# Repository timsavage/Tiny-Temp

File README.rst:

########
TinyTemp
########

Had all the components laying about so this is a bit of a trial project for 
making my first PCB. 

Utilises a HP QDSP-6064 bubble display, a TMP34 temperature sensor, and an 
ATTiny85, will draw very little current for a longer life.

Hardware
========

The bubble displays can be hard to come by but they do pop up on Ebay from 
time to time.

Display is driven by a pair of 74HC595 IC's, one to control segments the other 
to switch transistors to pull Cathodes to ground. As the 74HC595 can be daisy
chained on 3 pins are required to drive the display. The TMP36 uses 1 ADC 
leaving one pin free.

Note that in the schematic the 3.3 Volt regulator used is the LD33V the pin
layout differs from the 78XX series in with:
 - Pin 1: GRN
 - Pin 2: OUT
 - Pin 3: IN

The schematic uses a 78XX series symbol.

The ICSP header is optional and only really in place for convenience.

BOM
---

 - 1x HP QDSP-6064 - 7 Segment "Bubble" display
 - 1x	ATTiny 85
 - 1x	TMP34 - Temperature sensor
 - 1x LD33V - 3.3V voltage regulator
 - 2x	74HC595 - Shift register
 - 4x	2N3904 - NPN transistor
 - 5x	10k ohm resistor
 - 4x	330 ohm resistor
 - 2x	0.1uF MLC cap

Software
========

Use the install target to build, upload, and set correct fuses for an ATTiny85
using a USBTiny programmer. These settings can be tweaked in the Makefile.

All pins, voltage levels (defaults to 3.3V) can be configured in *defines.h*.

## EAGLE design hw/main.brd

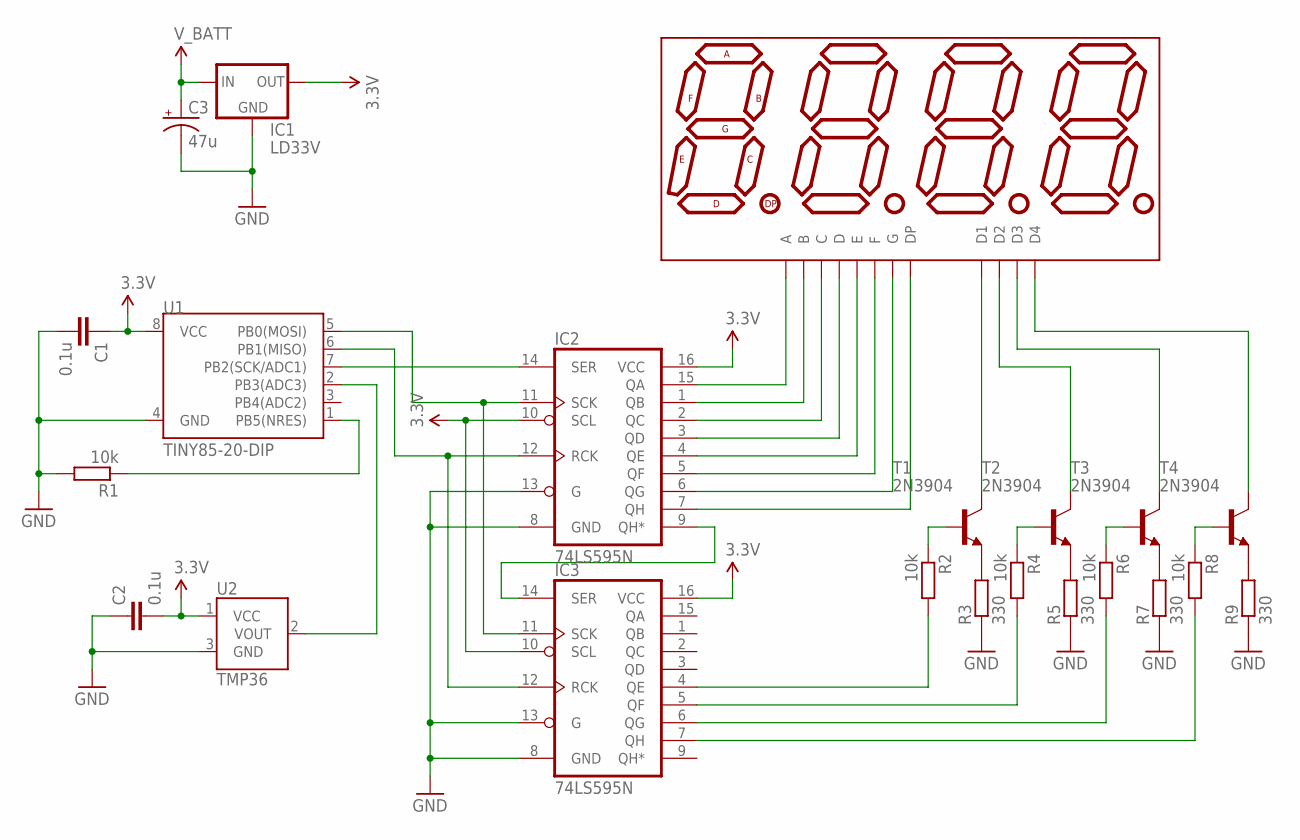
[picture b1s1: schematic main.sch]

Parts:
C1, C2: 0.1u; C025-025X050
C3: 47u; CPOL-RADIAL-10UF-25V
DISP1: 7-SEGMENT-4DIGIT-COUNTER-HP-BUBBLE; DIL12
IC1: LD33V; 78XXL
IC2, IC3: 74LS595N; DIL16
R1: 10k; 0204/7
R2, R4, R6, R8: 10k; 0204V
R3, R5, R7, R9: 330; 0204V
T1, T2, T3, T4: 2N3904; TO92
U1: TINY85-20-DIP; DIP08
U2: TMP36; TO-92

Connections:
GND: C1.2, C2.1, C3.2 (-), IC1.GND, IC2.8 (GND), IC2.13 (G), IC3.8 (GND), IC3.13 (G), R1.2, R3.1, R5.1, R7.1, R9.1, U1.4 (GND), U2.3 (GND); also elsewhere on the board
unnamed: DISP1.12 (A), IC2.15 (QA)
unnamed: DISP1.11 (B), IC2.1 (QB)
unnamed: DISP1.3 (C), IC2.2 (QC)
unnamed: DISP1.8 (D), IC2.3 (QD)
unnamed: DISP1.2 (E), IC2.4 (QE)
unnamed: DISP1.9 (F), IC2.5 (QF)
unnamed: DISP1.7 (G), IC2.6 (QG)
unnamed: DISP1.5 (DP), IC2.7 (QH)
unnamed: IC2.9 (QH*), IC3.14 (SER)
unnamed 10: IC2.11 (SCK), IC3.11 (SCK), U1.5 (PB0(MOSI)); also elsewhere on the board
unnamed 11: IC2.12 (RCK), IC3.12 (RCK), U1.6 (PB1(MISO)); also elsewhere on the board
unnamed: R3.2, T1.3 (E)
unnamed: R5.2, T2.3 (E)
unnamed: R9.2, T4.3 (E)
unnamed: R7.2, T3.3 (E)
unnamed: IC3.7 (QH), R8.2
unnamed: IC3.6 (QG), R6.2
unnamed: IC3.5 (QF), R4.2
unnamed: IC3.4 (QE), R2.2
unnamed: R2.1, T1.2 (B)
unnamed: R4.1, T2.2 (B)
unnamed: R6.1, T3.2 (B)
unnamed: R8.1, T4.2 (B)
unnamed: DISP1.1 (D1), T1.1 (C)
unnamed: DISP1.6 (D4), T4.1 (C)
unnamed: DISP1.4 (D3), T3.1 (C)
unnamed: DISP1.10 (D2), T2.1 (C)
unnamed: U1.2 (PB3(ADC3)), U2.2 (VOUT)
unnamed 29: R1.1, U1.1 (PB5(NRES)); also elsewhere on the board
unnamed 30: IC2.14 (SER), U1.7 (PB2(SCK/ADC1)); also elsewhere on the board
VCC: C1.1, C2.2, IC1.OUT, IC2.10 (SCL), IC2.16 (VCC), IC3.10 (SCL), IC3.16 (VCC), U1.8 (VCC), U2.1 (VCC)
V_BATT: C3.1 (+), IC1.IN; also elsewhere on the board

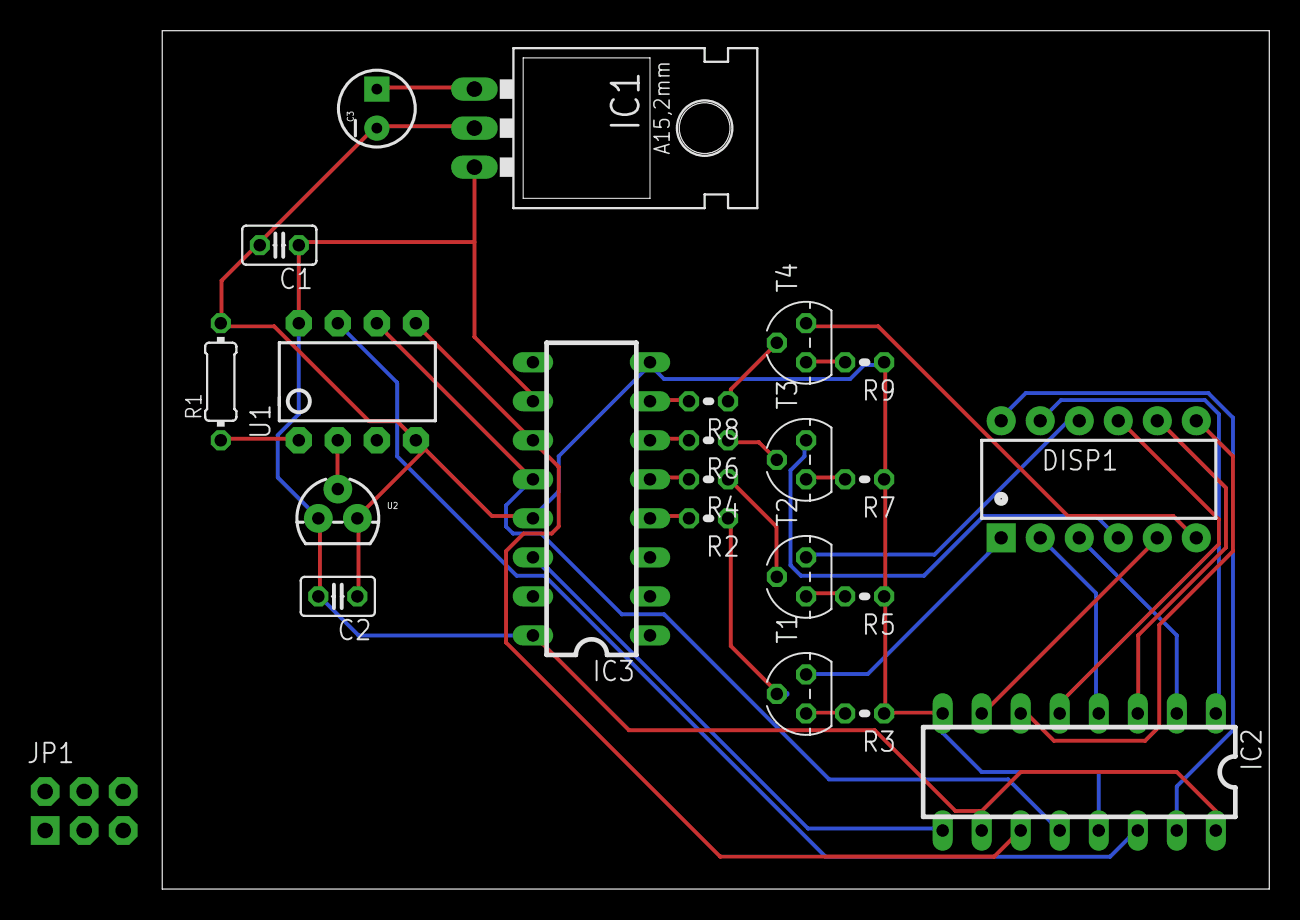
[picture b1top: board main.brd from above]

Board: 2 copper layers, 72.1 x 55.9 mm, 23 parts (0 on the bottom side), 33 nets.

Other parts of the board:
JP1: AVR_SPI_PRG_6NS; 2X3-NS

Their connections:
GND: JP1.6; also elsewhere on the board
unnamed 10: JP1.4; also elsewhere on the board
unnamed 11: JP1.1; also elsewhere on the board
unnamed 29: JP1.5; also elsewhere on the board
unnamed 30: JP1.3; also elsewhere on the board
V_BATT: JP1.2; also elsewhere on the board

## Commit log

2016-04-10 Added schematic for HW
2016-04-10 Added ICSP header
2016-04-10 Refactored temperature acquisition code to spread time across multiple cycles of the runloop. This is to reduce flicker on the display
2016-04-10 Added comments
2016-04-10 Added schematic
2016-04-10 Centered
2016-04-10 Added readme

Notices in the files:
parts and their libraries:
SparkFun-Capacitors: Licensing: Creative Commons ShareAlike 4.0 International - https://creativecommons.org/licenses/by-sa/4.0
